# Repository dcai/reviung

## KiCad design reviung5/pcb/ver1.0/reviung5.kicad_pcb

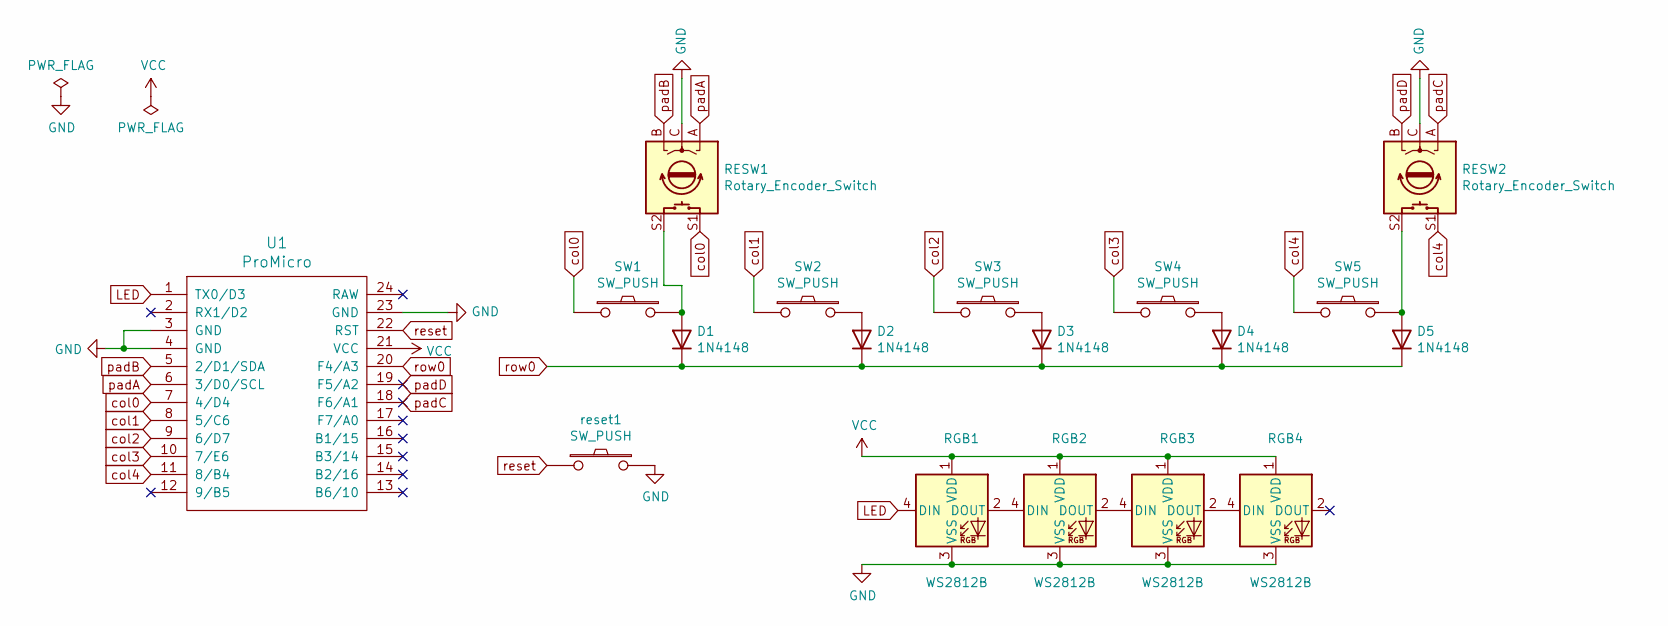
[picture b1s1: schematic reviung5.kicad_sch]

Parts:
D1, D2, D3, D4, D5: 1N4148; D3_TH_SMD_1side
RESW1, RESW2: Rotary_Encoder_Switch; RotaryEncoder_Alps_EC12E-Switch_Vertical_H20mm_CircularMoun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
RGB1, RGB2, RGB3, RGB4: WS2812B; LED_WS2812B_PLCC4_5.0x5.0mm_P3.2mm
SW1, SW5: SW_PUSH; MXOnly-1U-3pin
SW2, SW3, SW4: SW_PUSH; MXOnly-1U-NoLED
U1: ProMicro
reset1: SW_PUSH; ResetSW_TH_SMD

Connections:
GND: RESW1.C, RESW2.C, RGB1.3 (VSS), RGB2.3 (VSS), RGB3.3 (VSS), RGB4.3 (VSS), U1.3 (GND), U1.4 (GND), U1.23 (GND), reset1.2
LED: RGB1.4 (DIN), U1.1 (TX0/D3)
unnamed: D1.2 (A), RESW1.S2, SW1.2
unnamed: D2.2 (A), SW2.2
unnamed: D3.2 (A), SW3.2
unnamed: D4.2 (A), SW4.2
unnamed: D5.2 (A), RESW2.S2, SW5.2
unnamed: RGB1.2 (DOUT), RGB2.4 (DIN)
unnamed: RGB2.2 (DOUT), RGB3.4 (DIN)
unnamed: RGB3.2 (DOUT), RGB4.4 (DIN)
VCC: RGB1.1 (VDD), RGB2.1 (VDD), RGB3.1 (VDD), RGB4.1 (VDD), U1.21 (VCC)
col0: RESW1.S1, SW1.1, U1.7 (4/D4)
col1: SW2.1, U1.8 (5/C6)
col2: SW3.1, U1.9 (6/D7)
col3: SW4.1, U1.10 (7/E6)
col4: RESW2.S1, SW5.1, U1.11 (8/B4)
padA: RESW1.A, U1.6 (3/D0/SCL)
padB: RESW1.B, U1.5 (2/D1/SDA)
padC: RESW2.A, U1.18 (F6/A1)
padD: RESW2.B, U1.19 (F5/A2)
reset: U1.22 (RST), reset1.1
row0: D1.1 (K), D2.1 (K), D3.1 (K), D4.1 (K), D5.1 (K), U1.20 (F4/A3)

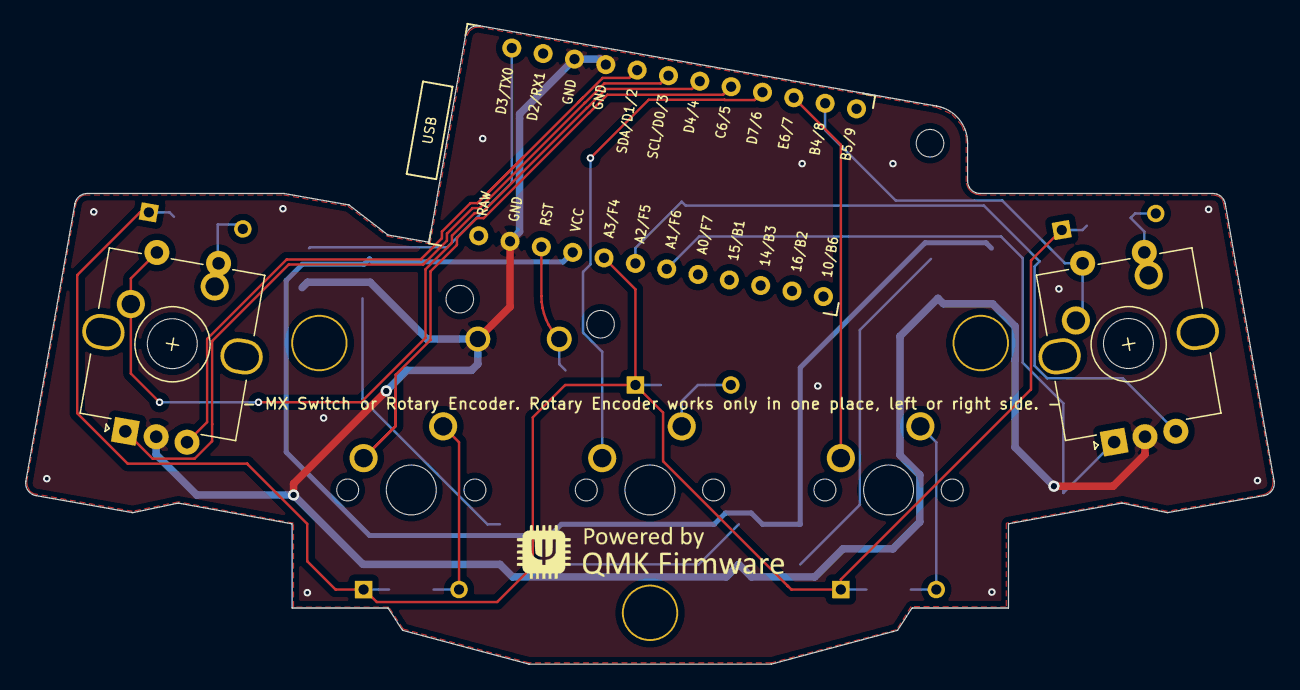
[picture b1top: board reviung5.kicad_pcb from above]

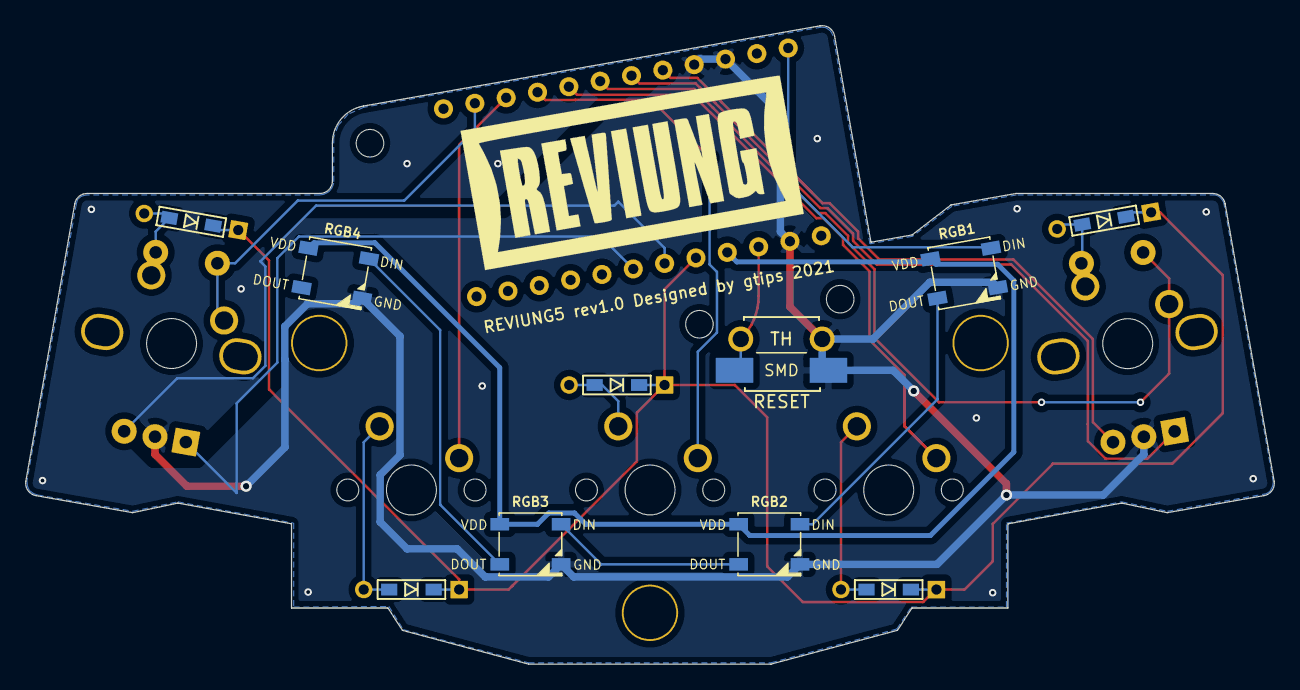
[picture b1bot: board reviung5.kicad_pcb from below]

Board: 2 copper layers, 99.7 x 51.0 mm, 21 parts (10 on the bottom side), 22 nets.

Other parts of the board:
Ref**: Val**; HOLE_2.2mm
Ref**#2, Ref**#3: Val**; HOLE_2.2mm

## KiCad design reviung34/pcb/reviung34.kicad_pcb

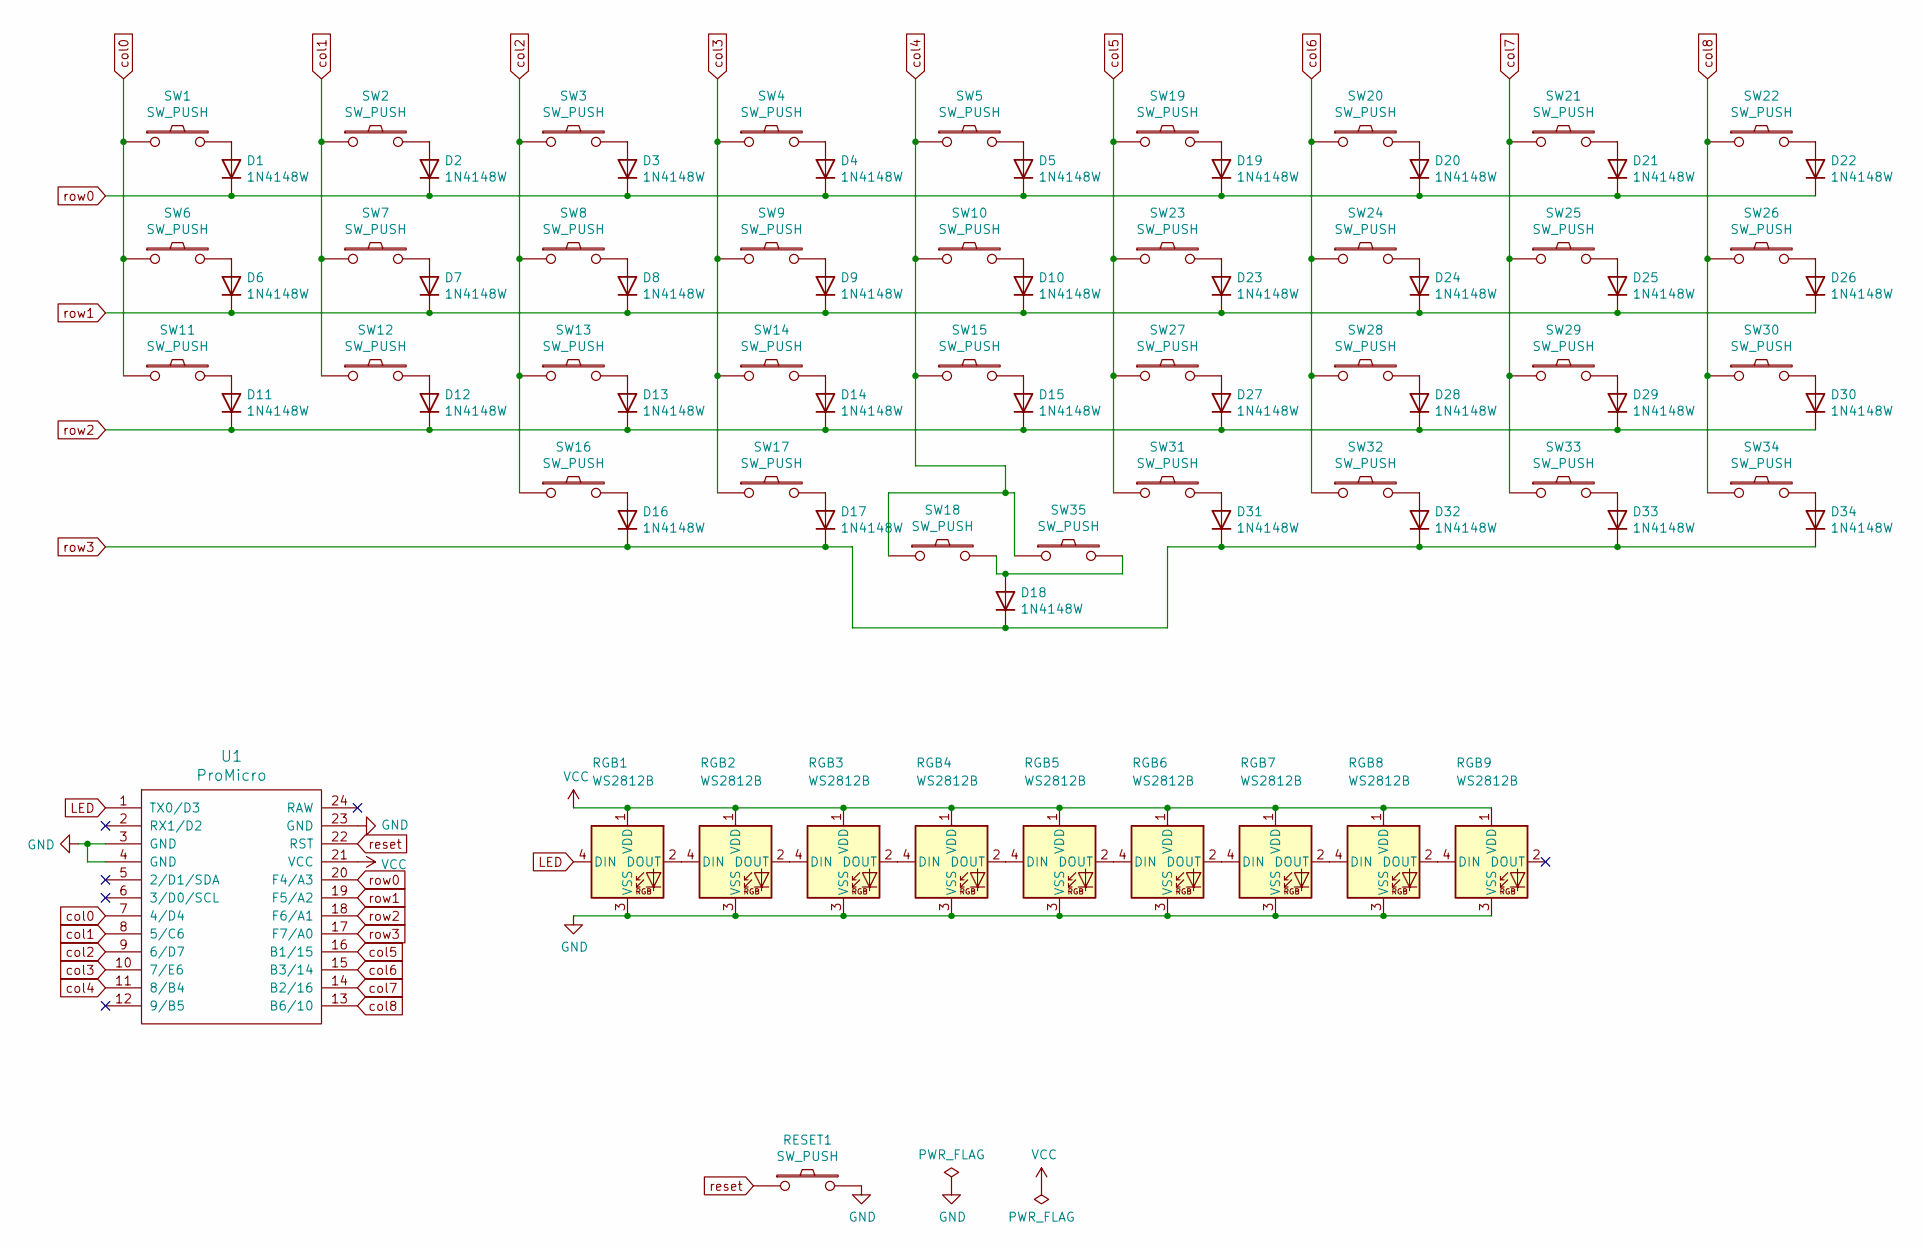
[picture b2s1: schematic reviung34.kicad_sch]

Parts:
D1: 1N4148W; SW_SPST_B3SL-1002P
D2, D3, D4, D5, D6, D7, D8, D9, D10, D11, D12, D13, D14, D15, D16, D17, D18, D19, D20, D21, D22, D23, D24, D25, D26, D27, D28, D29, D30, D31, D32, D33, D34: 1N4148W; Diode_SOD-123
RESET1: SW_PUSH; ResetSW_1side
RGB1, RGB2, RGB3, RGB4, RGB5, RGB6, RGB7, RGB8, RGB9: WS2812B; LED_WS2812B
SW1, SW2, SW3, SW4, SW5, SW6, SW7, SW8, SW9, SW10, SW11, SW12, SW13, SW14, SW15, SW16, SW17, SW18, SW19, SW20, SW21, SW22, SW23, SW24, SW25, SW26, SW27, SW28, SW29, SW30, SW31, SW32, SW33, SW34, SW35: SW_PUSH; Hotswap_MX_1.00u
U1: ProMicro; Arduino_Pro_Micro

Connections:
GND: RESET1.2, RGB1.3 (VSS), RGB2.3 (VSS), RGB3.3 (VSS), RGB4.3 (VSS), RGB5.3 (VSS), RGB6.3 (VSS), RGB7.3 (VSS), RGB8.3 (VSS), RGB9.3 (VSS), U1.3 (GND), U1.4 (GND), U1.23 (GND)
LED: RGB1.4 (DIN), U1.1 (TX0/D3)
unnamed: D1.2 (A), SW1.2
unnamed: D2.2 (A), SW2.2
unnamed: D3.2 (A), SW3.2
unnamed: D4.2 (A), SW4.2
unnamed: D5.2 (A), SW5.2
unnamed: D6.2 (A), SW6.2
unnamed: D7.2 (A), SW7.2
unnamed: D8.2 (A), SW8.2
unnamed: D9.2 (A), SW9.2
unnamed: D10.2 (A), SW10.2
unnamed: D11.2 (A), SW11.2
unnamed: D12.2 (A), SW12.2
unnamed: D13.2 (A), SW13.2
unnamed: D14.2 (A), SW14.2
unnamed: D15.2 (A), SW15.2
unnamed: D16.2 (A), SW16.2
unnamed: D17.2 (A), SW17.2
unnamed: D18.2 (A), SW18.2, SW35.2
unnamed: D19.2 (A), SW19.2
unnamed: D20.2 (A), SW20.2
unnamed: D21.2 (A), SW21.2
unnamed: D22.2 (A), SW22.2
unnamed: D23.2 (A), SW23.2
unnamed: D24.2 (A), SW24.2
unnamed: D25.2 (A), SW25.2
unnamed: D26.2 (A), SW26.2
unnamed: D27.2 (A), SW27.2
unnamed: D28.2 (A), SW28.2
unnamed: D29.2 (A), SW29.2
unnamed: D30.2 (A), SW30.2
unnamed: D31.2 (A), SW31.2
unnamed: D32.2 (A), SW32.2
unnamed: D33.2 (A), SW33.2
unnamed: D34.2 (A), SW34.2
unnamed: RGB1.2 (DOUT), RGB2.4 (DIN)
unnamed: RGB2.2 (DOUT), RGB3.4 (DIN)
unnamed: RGB3.2 (DOUT), RGB4.4 (DIN)
unnamed: RGB4.2 (DOUT), RGB5.4 (DIN)
unnamed: RGB5.2 (DOUT), RGB6.4 (DIN)
unnamed: RGB6.2 (DOUT), RGB7.4 (DIN)
unnamed: RGB7.2 (DOUT), RGB8.4 (DIN)
unnamed: RGB8.2 (DOUT), RGB9.4 (DIN)
VCC: RGB1.1 (VDD), RGB2.1 (VDD), RGB3.1 (VDD), RGB4.1 (VDD), RGB5.1 (VDD), RGB6.1 (VDD), RGB7.1 (VDD), RGB8.1 (VDD), RGB9.1 (VDD), U1.21 (VCC)
col0: SW1.1, SW6.1, SW11.1, U1.7 (4/D4)
col1: SW2.1, SW7.1, SW12.1, U1.8 (5/C6)
col2: SW3.1, SW8.1, SW13.1, SW16.1, U1.9 (6/D7)
col3: SW4.1, SW9.1, SW14.1, SW17.1, U1.10 (7/E6)
col4: SW5.1, SW10.1, SW15.1, SW18.1, SW35.1, U1.11 (8/B4)
col5: SW19.1, SW23.1, SW27.1, SW31.1, U1.16 (B1/15)
col6: SW20.1, SW24.1, SW28.1, SW32.1, U1.15 (B3/14)
col7: SW21.1, SW25.1, SW29.1, SW33.1, U1.14 (B2/16)
col8: SW22.1, SW26.1, SW30.1, SW34.1, U1.13 (B6/10)
reset: RESET1.1, U1.22 (RST)
row0: D1.1 (K), D2.1 (K), D3.1 (K), D4.1 (K), D5.1 (K), D19.1 (K), D20.1 (K), D21.1 (K), D22.1 (K), U1.20 (F4/A3)
row1: D6.1 (K), D7.1 (K), D8.1 (K), D9.1 (K), D10.1 (K), D23.1 (K), D24.1 (K), D25.1 (K), D26.1 (K), U1.19 (F5/A2)
row2: D11.1 (K), D12.1 (K), D13.1 (K), D14.1 (K), D15.1 (K), D27.1 (K), D28.1 (K), D29.1 (K), D30.1 (K), U1.18 (F6/A1)
row3: D16.1 (K), D17.1 (K), D18.1 (K), D31.1 (K), D32.1 (K), D33.1 (K), D34.1 (K), U1.17 (F7/A0)

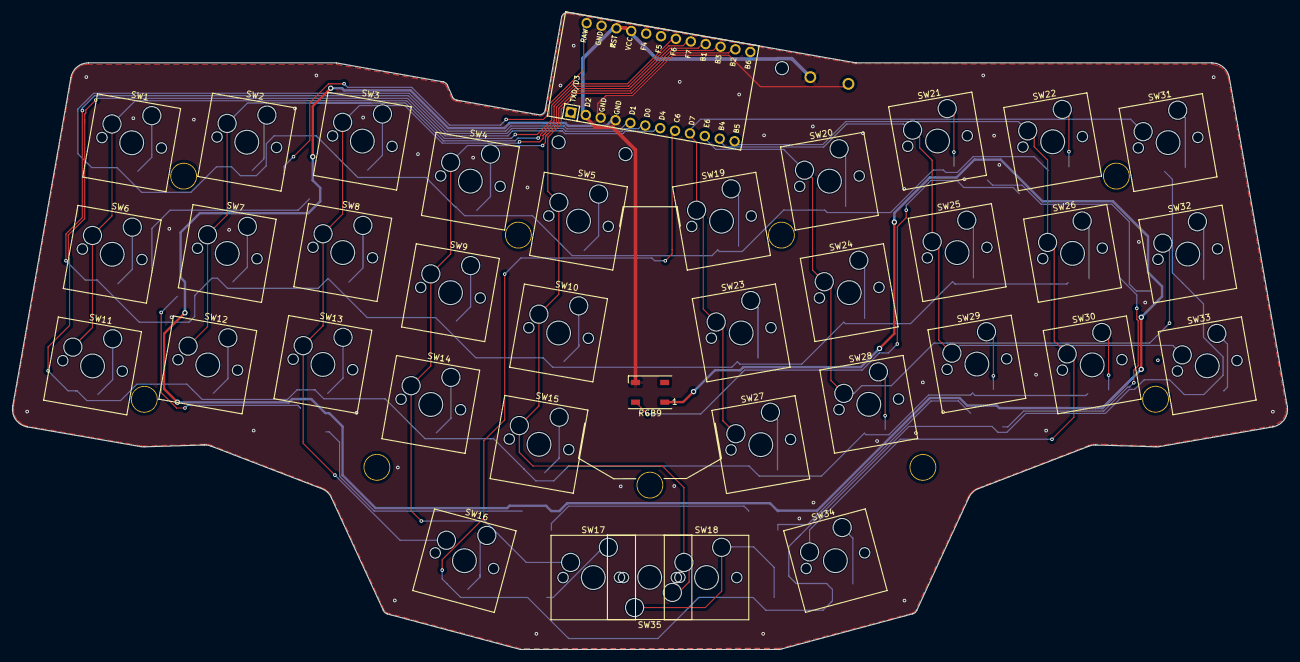
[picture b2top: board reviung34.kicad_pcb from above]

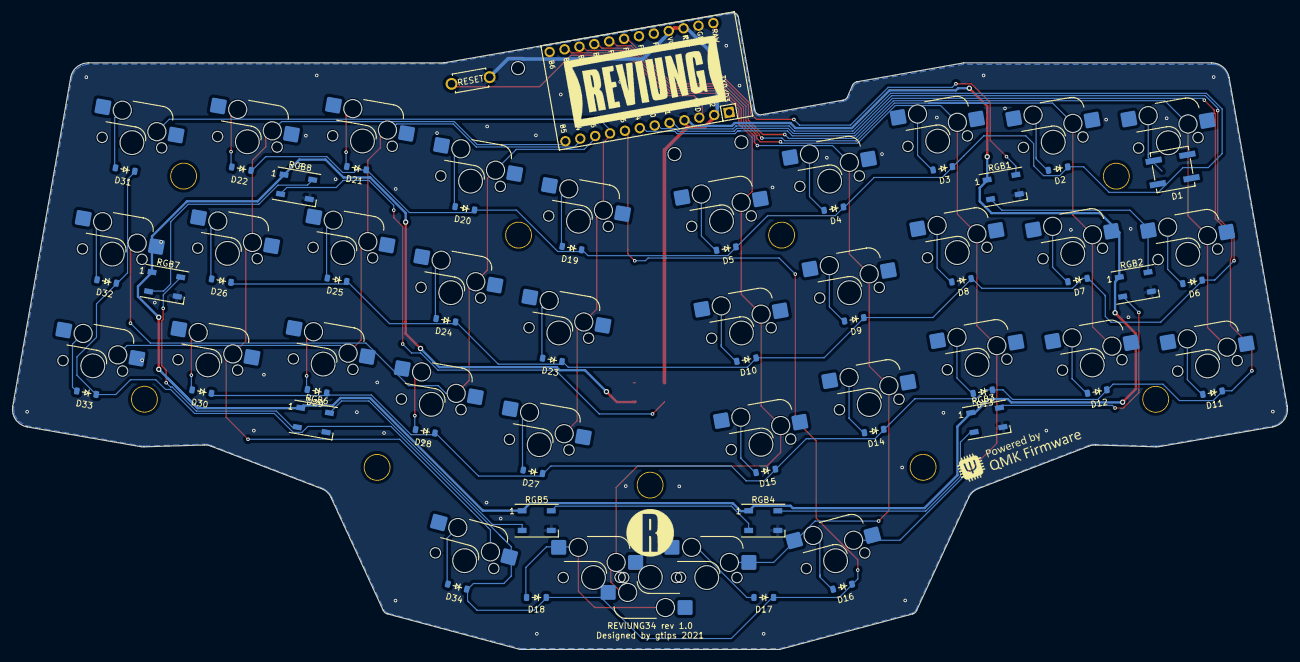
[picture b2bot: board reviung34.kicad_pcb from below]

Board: 2 copper layers, 214.3 x 107.1 mm, 92 parts (43 on the bottom side), 59 nets.

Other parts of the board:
H1, H2, H3, H4, H5, H6, H7, H8, H9: HOLE_4.2mm
Ref**: Val**; HOLE_2.2mm
Ref**#2, Ref**#3: Val**; HOLE_2.2mm

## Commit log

2023-10-02 reviung34: hotswap
2023-10-03 reviung5: two encoders
2023-10-03 reviung34: circuit updates
